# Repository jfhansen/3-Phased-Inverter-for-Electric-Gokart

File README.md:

# 3-Phased-Inverter-for-Electric-Gokart
Repository containing Simulation files, PCB files and embedded software for three-phased inverter drive.

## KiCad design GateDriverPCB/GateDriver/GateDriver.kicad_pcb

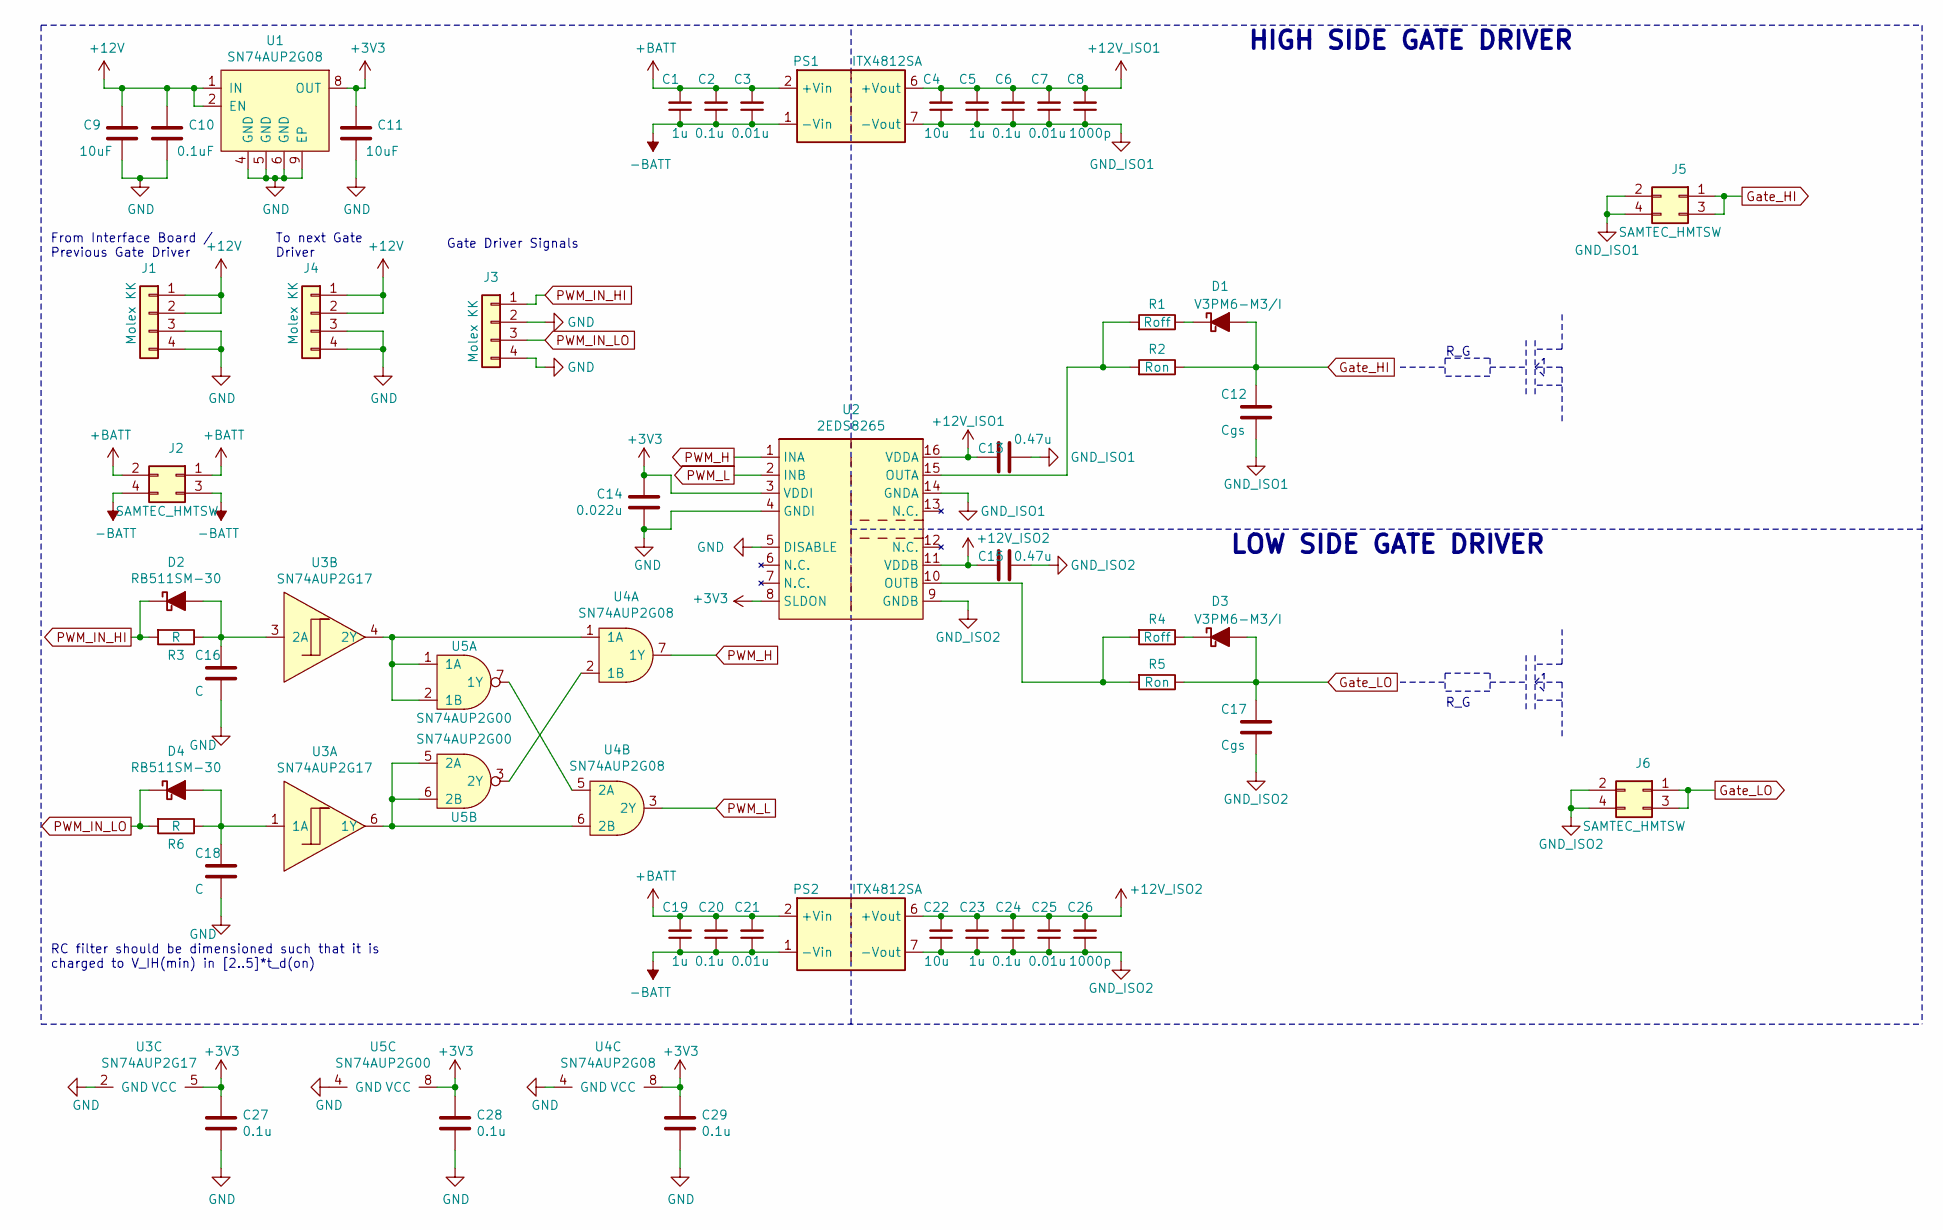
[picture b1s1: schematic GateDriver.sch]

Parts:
C1, C5, C19, C23: 1u; C_0805_2012Metric
C2, C6, C20, C24, C27, C28, C29: 0.1u; C_0805_2012Metric
C3, C7, C21, C25: 0.01u; C_0805_2012Metric
C4, C22: 10u; C_0805_2012Metric
C8, C26: 1000p; C_0805_2012Metric
C9, C11: 10uF; C_0805_2012Metric
C10: 0.1uF; C_0805_2012Metric
C12, C17: Cgs; C_0805_2012Metric
C13, C15: 0.47u; C_0805_2012Metric
C14: 0.022u; C_0805_2012Metric
C16, C18: C; C_0805_2012Metric
D1, D3: V3PM6-M3/I; D_SMP_DO-220AA
D2, D4: RB511SM-30; D_SOD-523
J1, J3, J4: Molex KK; Molex_KK-254_AE-6410-04A_1x04_P2.54mm_Vertical
J2, J5, J6: SAMTEC_HMTSW; PinHeader_2x02_P2.54mm_Vertical; Part No. HMTSW-102-22-L-D-370
PS1, PS2: ITX4812SA; Converter_DCDC_XP_POWER-ITXxxxxSA_THT
R1, R4: Roff; R_1206_3216Metric
R2, R5: Ron; R_1206_3216Metric
R3, R6: R; R_0805_2012Metric
U1: SN74AUP2G08; TI-VSSOP-8-PowerPAD
U2: 2EDS8265; PG-DSO-16-30
U3: SN74AUP2G17; DCK_R-PDSO-G6
U4: SN74AUP2G08; R-PDSO-G8
U5: SN74AUP2G00; R-PDSO-G8

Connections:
+3V3: C11.2, C14.1, C27.1, C28.1, C29.1, U1.8 (OUT), U2.3 (VDDI), U2.8 (SLDON), U3.5 (VCC), U4.8 (VCC), U5.8 (VCC)
+12V: C9.2, C10.2, J1.1, J1.2, J4.1, J4.2, U1.1 (IN), U1.2 (EN)
+12V_ISO1: C4.2, C5.2, C6.2, C7.2, C8.2, C13.2, PS1.6 (+Vout), U2.16 (VDDA)
+12V_ISO2: C15.2, C22.2, C23.2, C24.2, C25.2, C26.2, PS2.6 (+Vout), U2.11 (VDDB)
+BATT: C1.2, C2.2, C3.2, C19.2, C20.2, C21.2, J2.1, J2.2, PS1.2 (+Vin), PS2.2 (+Vin)
-BATT: C1.1, C2.1, C3.1, C19.1, C20.1, C21.1, J2.3, J2.4, PS1.1 (-Vin), PS2.1 (-Vin)
GND: C9.1, C10.1, C11.1, C14.2, C16.2, C18.2, C27.2, C28.2, C29.2, J1.3, J1.4, J3.2, J3.4, J4.3, J4.4, U1.4 (GND), U1.5 (GND), U1.6 (GND), U1.9 (EP), U2.4 (GNDI), U2.5 (DISABLE), U3.2 (GND), U4.4 (GND), U5.4 (GND)
GND_ISO1: C4.1, C5.1, C6.1, C7.1, C8.1, C12.2, C13.1, J5.2, J5.4, PS1.7 (-Vout), U2.14 (GNDA)
GND_ISO2: C15.1, C17.2, C22.1, C23.1, C24.1, C25.1, C26.1, J6.2, J6.4, PS2.7 (-Vout), U2.9 (GNDB)
Gate_HI: C12.1, D1.2 (A), J5.1, J5.3, R2.1
Gate_LO: C17.1, D3.2 (A), J6.1, J6.3, R5.1
unnamed: C16.1, D2.2 (A), R3.1, U3.3 (2A)
unnamed: C18.1, D4.2 (A), R6.1, U3.1 (1A)
unnamed: D1.1 (K), R1.1
unnamed: D3.1 (K), R4.1
unnamed: R1.2, R2.2, U2.15 (OUTA)
unnamed: R4.2, R5.2, U2.10 (OUTB)
unnamed: U3.4 (2Y), U4.1 (1A), U5.1 (1A), U5.2 (1B)
unnamed: U3.6 (1Y), U4.6 (2B), U5.5 (2A), U5.6 (2B)
unnamed: U4.2 (1B), U5.3 (2Y)
unnamed: U4.5 (2A), U5.7 (1Y)
PWM_H: U2.1 (INA), U4.7 (1Y)
PWM_IN_HI: D2.1 (K), J3.1, R3.2
PWM_IN_LO: D4.1 (K), J3.3, R6.2
PWM_L: U2.2 (INB), U4.3 (2Y)

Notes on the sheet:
HIGH SIDE GATE DRIVER
LOW SIDE GATE DRIVER
RC filter should be dimensioned such that it is charged to V_IH(min) in [2..5]*t_d(on)
R_G
From Interface Board / Previous Gate Driver
To next Gate Driver
Gate Driver Signals

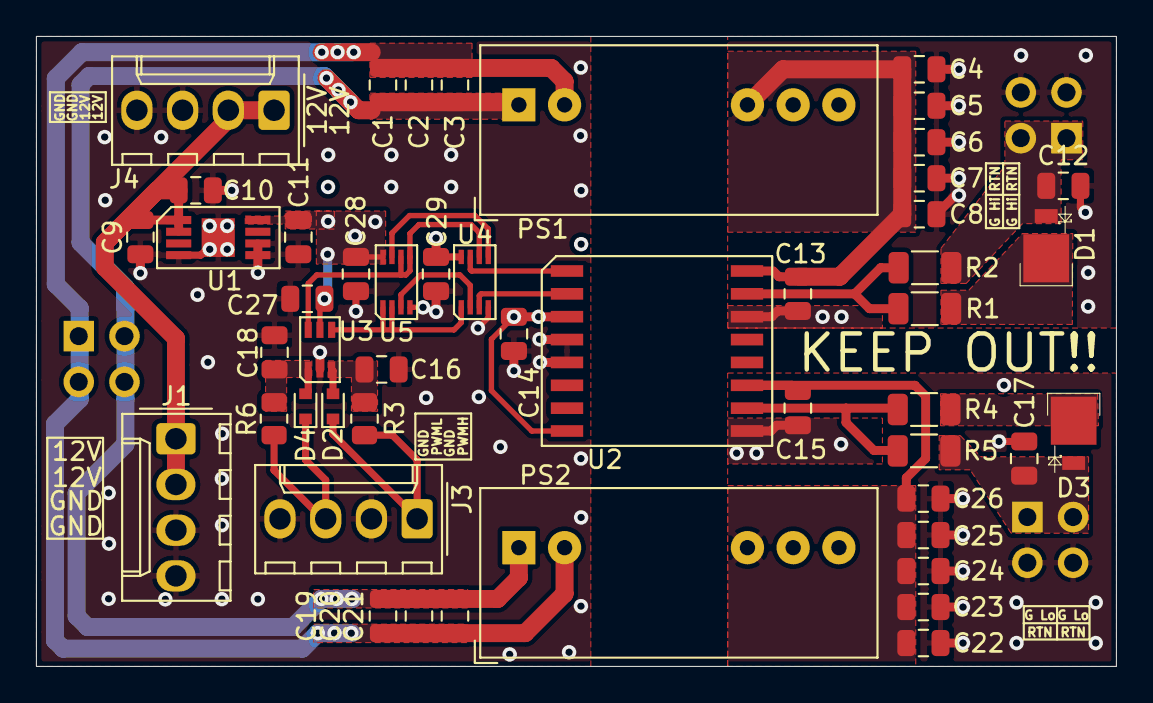
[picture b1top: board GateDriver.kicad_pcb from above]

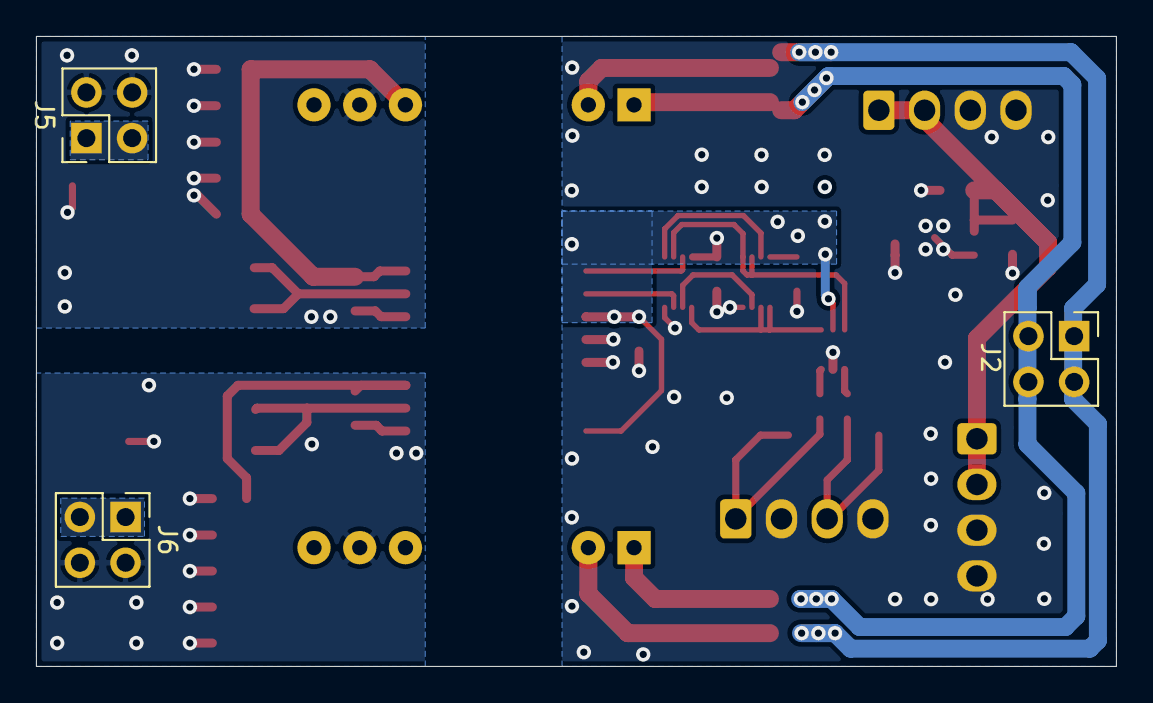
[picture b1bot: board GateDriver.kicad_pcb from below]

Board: 2 copper layers, 60.0 x 35.0 mm, 52 parts (3 on the bottom side), 25 nets.

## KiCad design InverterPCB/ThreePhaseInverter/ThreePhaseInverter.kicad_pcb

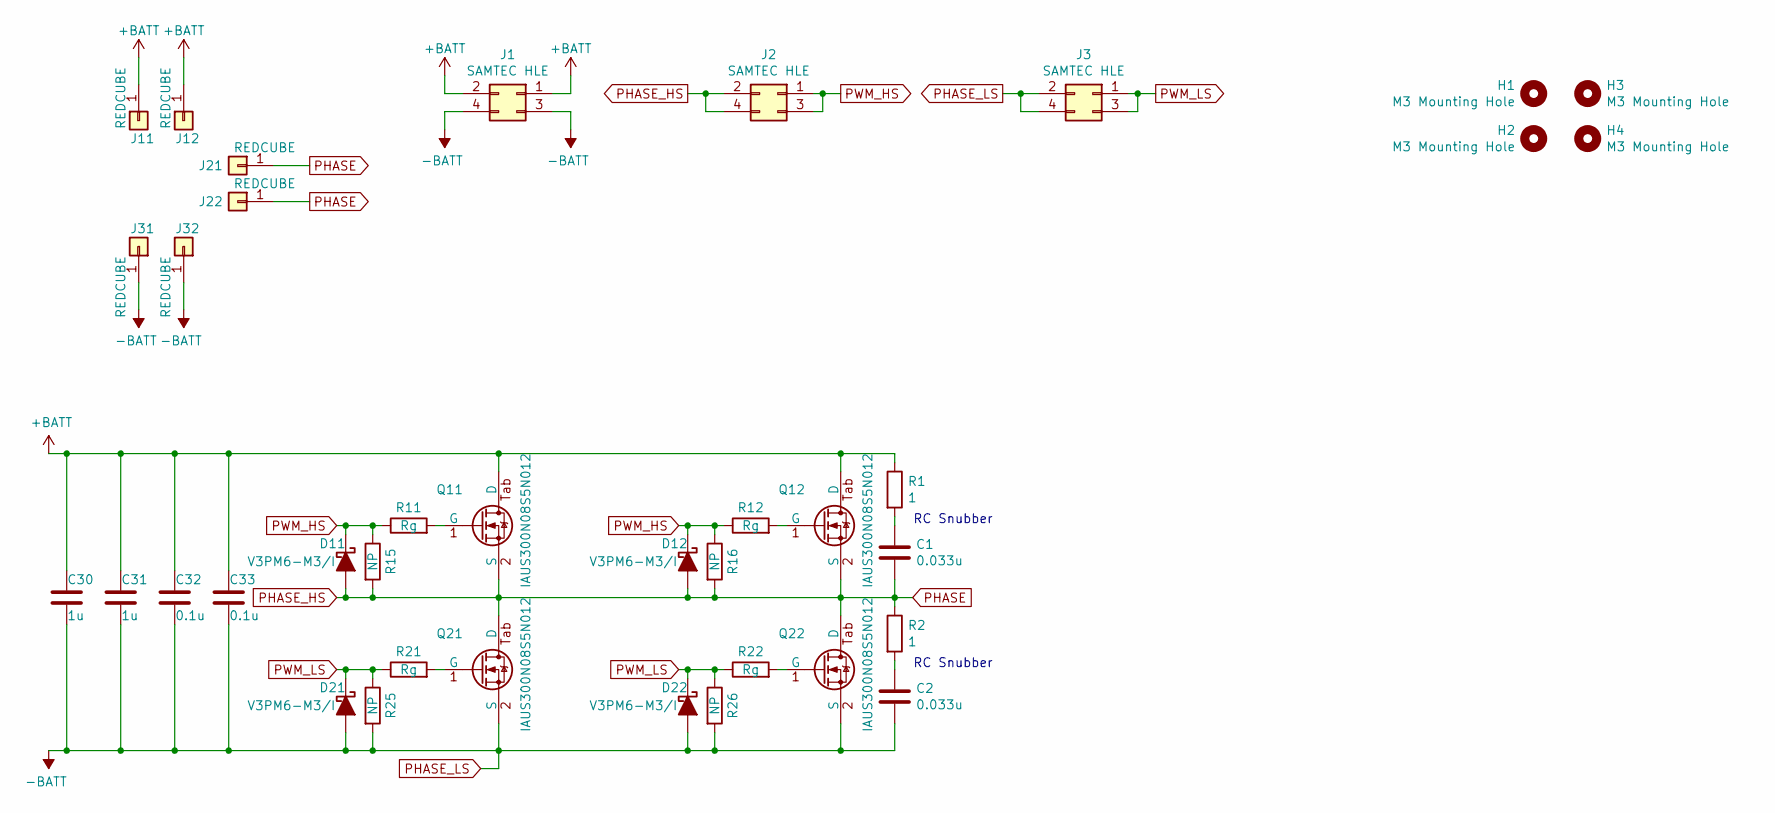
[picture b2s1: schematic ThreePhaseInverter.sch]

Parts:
C1, C2: 0.033u; C_1206_3216Metric_Pad1.33x1.80mm_HandSolder
C30, C31: 1u; C_1206_3216Metric_Pad1.33x1.80mm_HandSolder
C32, C33: 0.1u; C_1206_3216Metric_Pad1.33x1.80mm_HandSolder
D11, D12, D21, D22: V3PM6-M3/I; D_SMP_DO-220AA
H1, H2, H3, H4: M3 Mounting Hole; MountingHole_3.2mm_M3_ISO7380_Pad
J1, J2, J3: SAMTEC HLE; Samtec_HLE-102-02-xxx-DV_2x02_P2.54mm_Horizontal
J11, J12, J21, J22, J31, J32: REDCUBE; Würth_7466205
Q11, Q12, Q21, Q22: IAUS300N08S5N012; Infineon_PG-HSOG-8-1
R1, R2: 1; R_1206_3216Metric_Pad1.30x1.75mm_HandSolder
R11, R12, R21, R22: Rg; R_1206_3216Metric_Pad1.30x1.75mm_HandSolder
R15, R16, R25, R26: NP; R_0805_2012Metric_Pad1.20x1.40mm_HandSolder

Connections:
+BATT: C30.1, C31.1, C32.1, C33.1, J1.1, J1.2, J11.1, J12.1, Q11.Tab (D), Q12.Tab (D), R1.1
unnamed: C1.1, R1.2
unnamed: C2.1, R2.2
unnamed: Q11.1 (G), R11.2
unnamed: Q12.1 (G), R12.2
unnamed: Q21.1 (G), R21.2
unnamed: Q22.1 (G), R22.2
PHASE: C1.2, D11.2 (A), D12.2 (A), J2.2, J2.4, J21.1, J22.1, Q11.2 (S), Q11.3 (S), Q11.4 (S), Q11.5 (S), Q11.6 (S), Q11.7 (S), Q11.8 (S), Q12.2 (S), Q12.3 (S), Q12.4 (S), Q12.5 (S), Q12.6 (S), Q12.7 (S), Q12.8 (S), Q21.Tab (D), Q22.Tab (D), R2.1, R15.2, R16.2
PHASE_LS: C2.2, C30.2, C31.2, C32.2, C33.2, D21.2 (A), D22.2 (A), J1.3, J1.4, J3.2, J3.4, J31.1, J32.1, Q21.2 (S), Q21.3 (S), Q21.4 (S), Q21.5 (S), Q21.6 (S), Q21.7 (S), Q21.8 (S), Q22.2 (S), Q22.3 (S), Q22.4 (S), Q22.5 (S), Q22.6 (S), Q22.7 (S), Q22.8 (S), R25.2, R26.2
PWM_HS: D11.1 (K), D12.1 (K), J2.1, J2.3, R11.1, R12.1, R15.1, R16.1
PWM_LS: D21.1 (K), D22.1 (K), J3.1, J3.3, R21.1, R22.1, R25.1, R26.1

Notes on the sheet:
RC Snubber

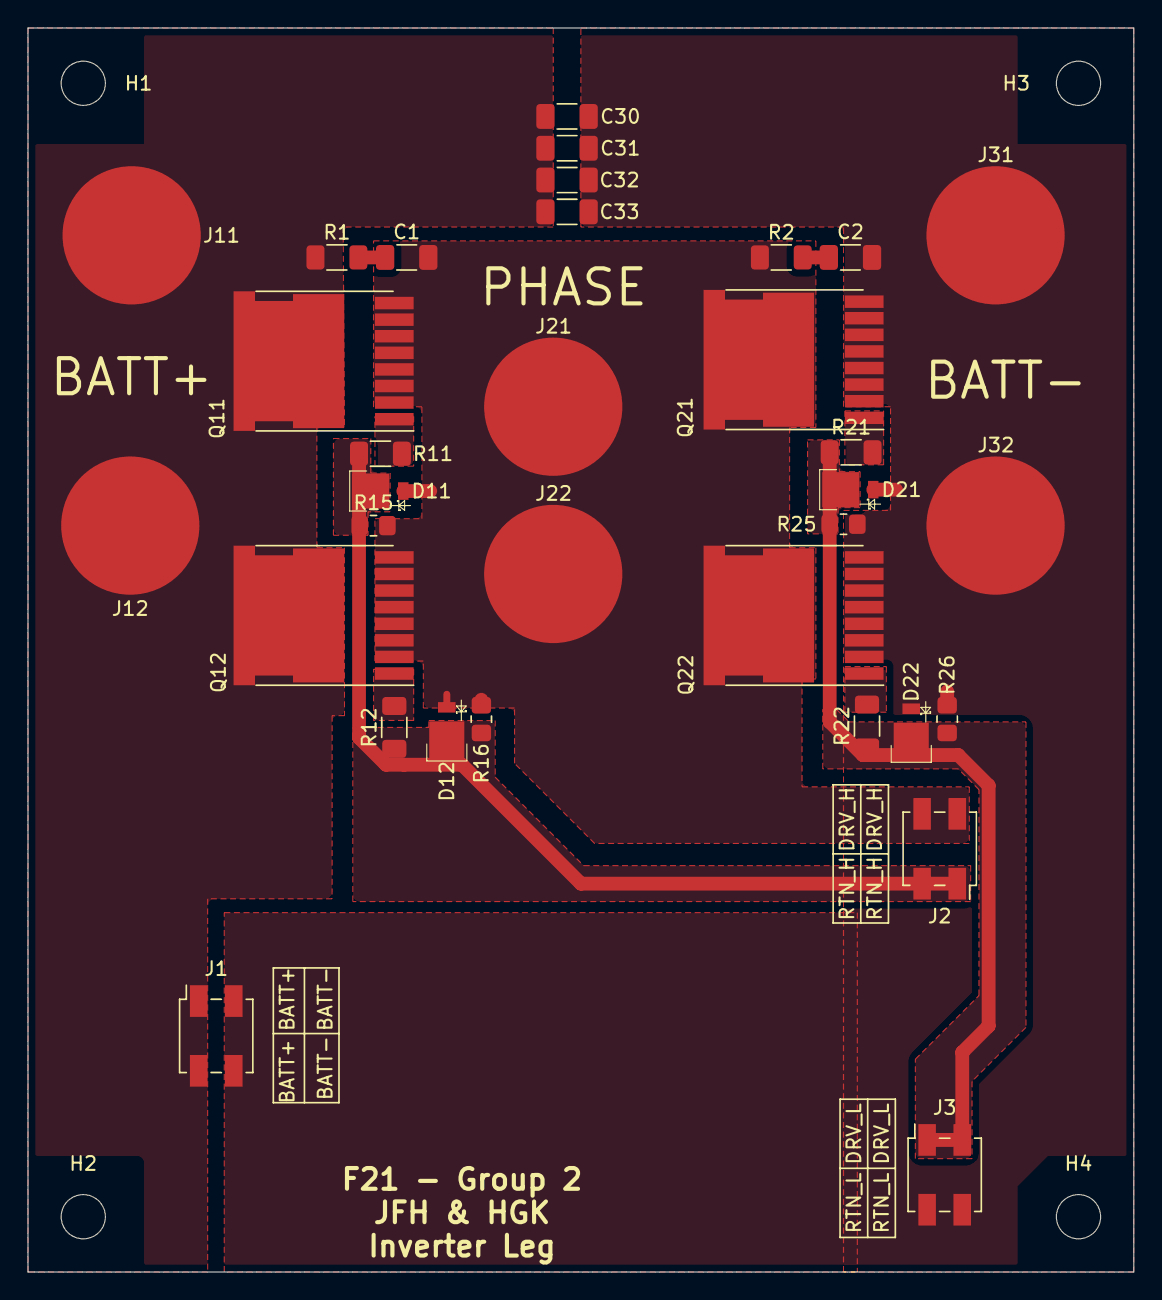
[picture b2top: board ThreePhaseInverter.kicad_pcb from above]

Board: 2 copper layers, 80.0 x 90.0 mm, 37 parts (0 on the bottom side), 11 nets.

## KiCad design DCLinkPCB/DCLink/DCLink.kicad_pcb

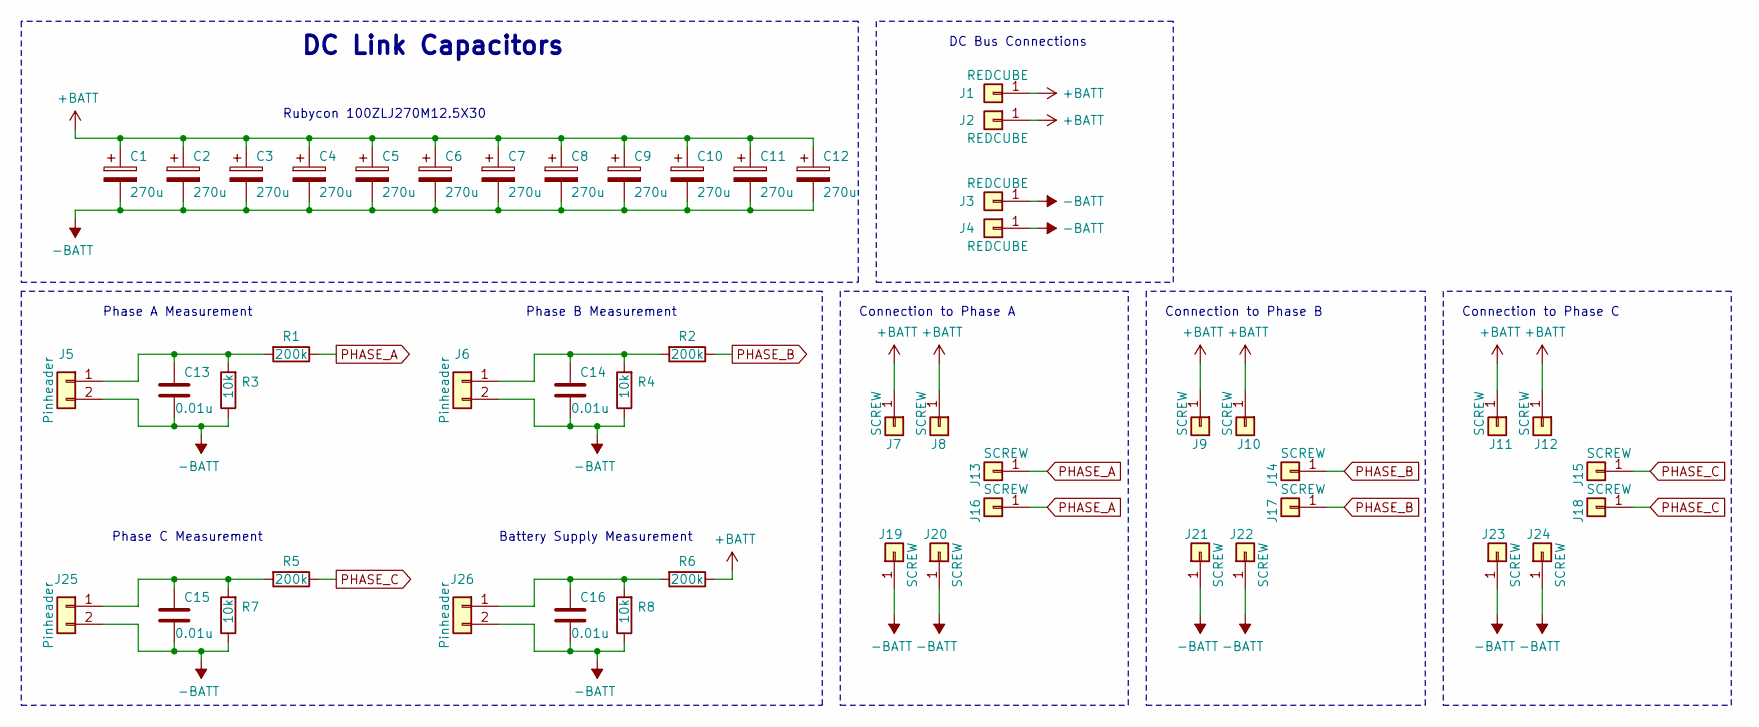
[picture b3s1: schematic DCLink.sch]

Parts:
C1, C2, C3, C4, C5, C6, C7, C8, C9, C10, C11, C12: 270u; CP_Radial_D12.5mm_P5.00mm; Man. Part No. 100ZLJ270M12.5X30
C13, C14, C15, C16: 0.01u; C_0805_2012Metric
J1, J2, J3, J4: REDCUBE; Würth_7466205
J5, J6, J25, J26: Pinheader; PinHeader_1x02_P2.54mm_Vertical
J7, J8, J9, J10, J11, J12, J13, J14, J15, J16, J17, J18, J19, J20, J21, J22, J23, J24: SCREW; MountingHole_5.3mm_M5_ISO7380_Pad
R1, R2, R5, R6: 200k; R_0805_2012Metric
R3, R4, R7, R8: 10k; R_0805_2012Metric

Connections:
+BATT: C1.1, C2.1, C3.1, C4.1, C5.1, C6.1, C7.1, C8.1, C9.1, C10.1, C11.1, C12.1, J1.1, J2.1, J7.1, J8.1, J9.1, J10.1, J11.1, J12.1, R6.1
-BATT: C1.2, C2.2, C3.2, C4.2, C5.2, C6.2, C7.2, C8.2, C9.2, C10.2, C11.2, C12.2, C13.2, C14.2, C15.2, C16.2, J3.1, J4.1, J5.2, J6.2, J19.1, J20.1, J21.1, J22.1, J23.1, J24.1, J25.2, J26.2, R3.1, R4.1, R7.1, R8.1
unnamed: C13.1, J5.1, R1.2, R3.2
unnamed: C14.1, J6.1, R2.2, R4.2
unnamed: C15.1, J25.1, R5.2, R7.2
unnamed: C16.1, J26.1, R6.2, R8.2
PHASE_A: J13.1, J16.1, R1.1
PHASE_B: J14.1, J17.1, R2.1
PHASE_C: J15.1, J18.1, R5.1

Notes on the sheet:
DC Link Capacitors
Rubycon 100ZLJ270M12.5X30
Phase A Measurement
Phase B Measurement
Phase C Measurement
Battery Supply Measurement
Connection to Phase A
Connection to Phase B
Connection to Phase C
DC Bus Connections

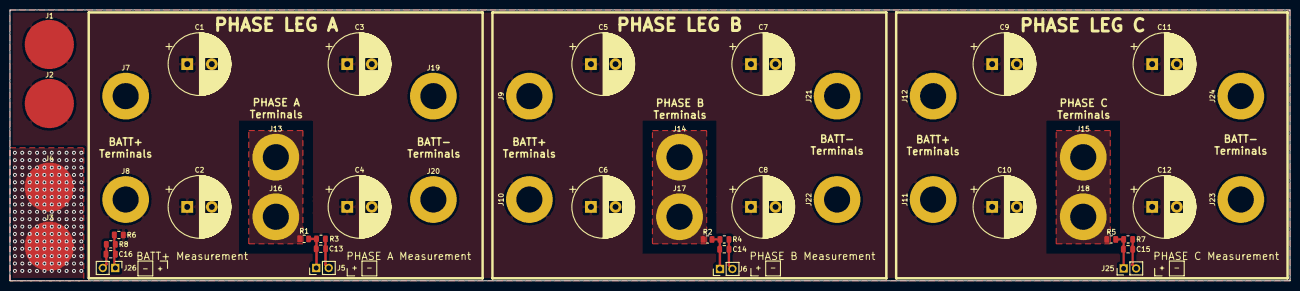
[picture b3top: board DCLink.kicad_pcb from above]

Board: 2 copper layers, 260.0 x 55.0 mm, 50 parts (0 on the bottom side), 9 nets.

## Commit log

2021-04-02 Started work on schematic for gate driver PCB. Added schematic symbols and footprints in Library folder.
2021-04-12 Finished Gate Driver Schematic. Only connectors for connection to Inverter PCB need to be placed.
2021-04-16 Finished PCB layout for Gate Driver, Inverter Leg and DC Link PCB.
